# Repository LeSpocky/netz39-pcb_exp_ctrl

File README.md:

Laborssteuerung
===============

Steuergeräte für unser PCB-Labor

# AC Switch
µC-Steuerbares Relais für 230V-Geräte mit Feedback zum Stromfluss
Anschluss über I³C

# Power Board
alle passiven Schalter:
2x Relais für 230V-Anschluss (Deckenlicht, Luftpumpe Ätzbad)
4x FET für 12V (2x LED-Strip rot, 1x LED-Strip weiß, 1x UV-Licht)

PCB Exposure Control (alex)
====================
We have a box with 40 UV LEDs …

Parts
-----
* LP2950

ToDo
----
* add 74xx165 for input keys and optionally 74xx14 against contact bounce

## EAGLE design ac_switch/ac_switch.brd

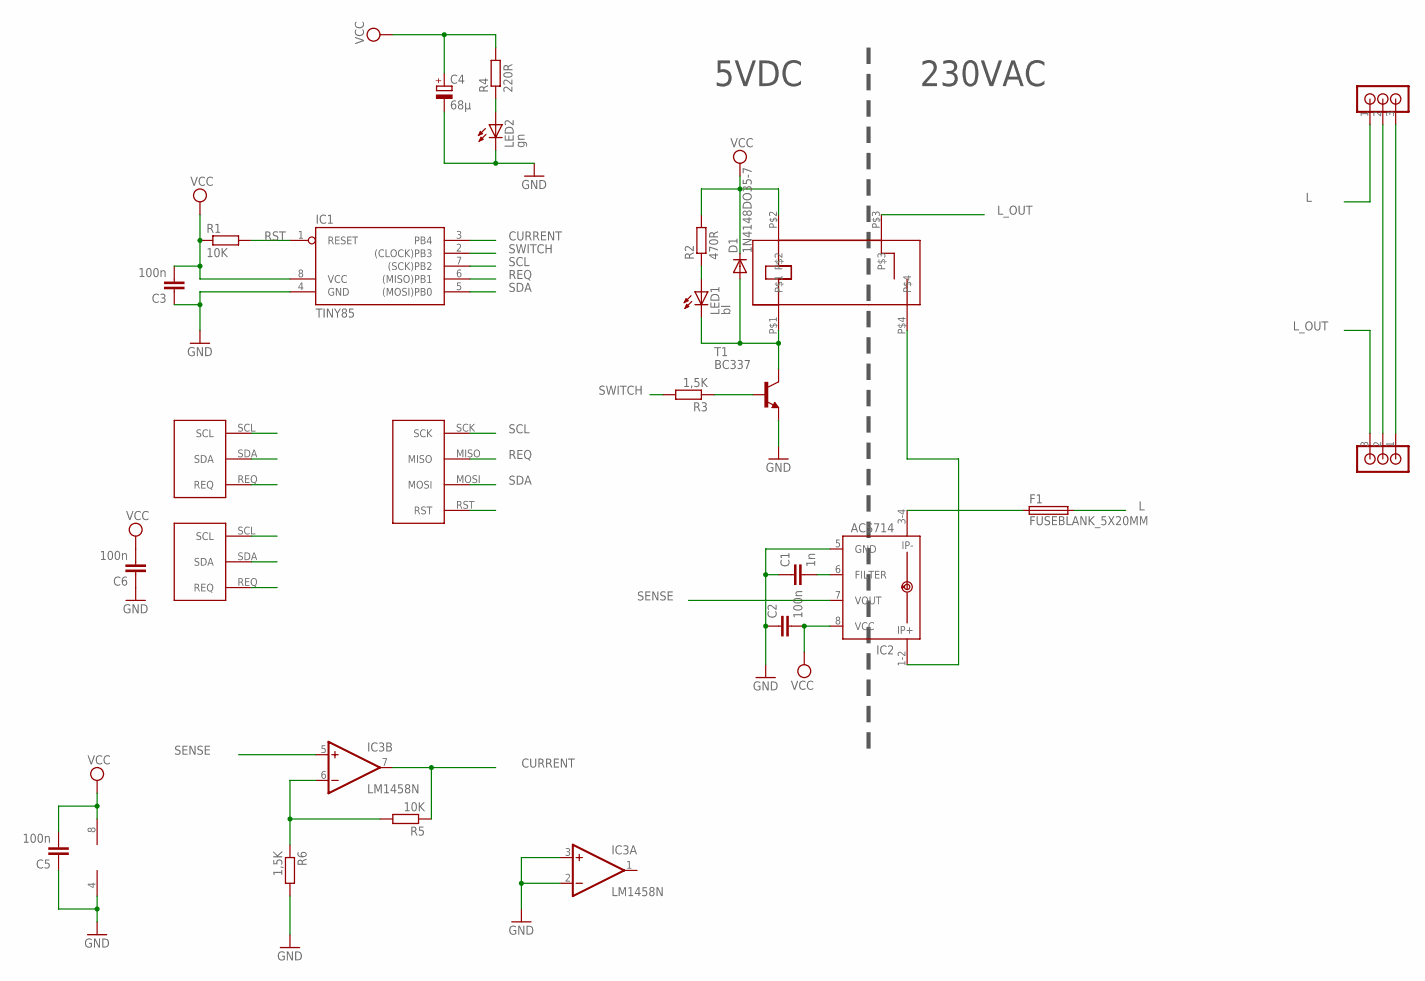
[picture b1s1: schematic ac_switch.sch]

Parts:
C1: 1n; C025-024X044
C2, C3, C5, C6: 100n; C025-024X044
C4: 68µ; E3,5-8
D1: 1N4148DO35-7; DO35-7
F1: FUSEBLANK_5X20MM; FUSE_HOLDER_5X20MM
IC1: TINY85; DIL08
IC2: ACS714
IC3: LM1458N; DIL08
LED1: bl; LED3MM
LED2: gn; LED3MM
R1: 10K; 0207/12
R2: 470R; 0207/10
R3, R6: 1,5K; 0207/10
R4: 220R; 0207/10
R5: 10K; 0207/10
T1: BC337; TO92
U$1: JS_05_MN_KT
U$2, U$6: RIACON_101_3
U$3, U$5: I3C_PORT; I3C_PADS
U$4: AVR_ISP

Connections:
CURRENT: IC1.3 (PB4), IC3.7 (OUT), R5.1
GND: C1.1, C2.1, C3.1, C4.-, C5.1, C6.1, IC1.4 (GND), IC2.5 (GND), IC3.2 (-IN), IC3.3 (+IN), IC3.4 (V-), LED2.K (C), R6.2, T1.1 (E), U$3.GND, U$4.GND, U$5.GND
L: F1.2, U$2.1
L_OUT: U$1.P$3, U$6.3
unnamed: D1.A, LED1.K (C), T1.3 (C), U$1.P$1
unnamed: C1.2, IC2.6 (FILTER)
unnamed: IC2.1-2 (IP+), U$1.P$4
unnamed: LED1.A, R2.1
unnamed: R3.1, T1.2 (B)
unnamed: LED2.A, R4.1
unnamed: F1.1, IC2.3-4 (IP-)
unnamed: U$2.3, U$6.1
unnamed: U$2.2, U$6.2
unnamed: IC3.6 (-IN), R5.2, R6.1
REQ: IC1.6 ((MISO)PB1), U$3.REQ, U$4.MISO, U$5.REQ
RST: IC1.1 (RESET), R1.2, U$4.RST
SCL: IC1.7 ((SCK)PB2), U$3.SCL, U$4.SCK, U$5.SCL
SDA: IC1.5 ((MOSI)PB0), U$3.SDA, U$4.MOSI, U$5.SDA
SENSE: IC2.7 (VOUT), IC3.5 (+IN)
SWITCH: IC1.2 ((CLOCK)PB3), R3.2
VCC: C2.2, C3.2, C4.+, C5.2, C6.2, D1.C, IC1.8 (VCC), IC2.8 (VCC), IC3.8 (V+), R1.1, R2.2, R4.2, U$1.P$2, U$3.VCC, U$4.VCC, U$5.VCC

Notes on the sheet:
230VAC
5VDC

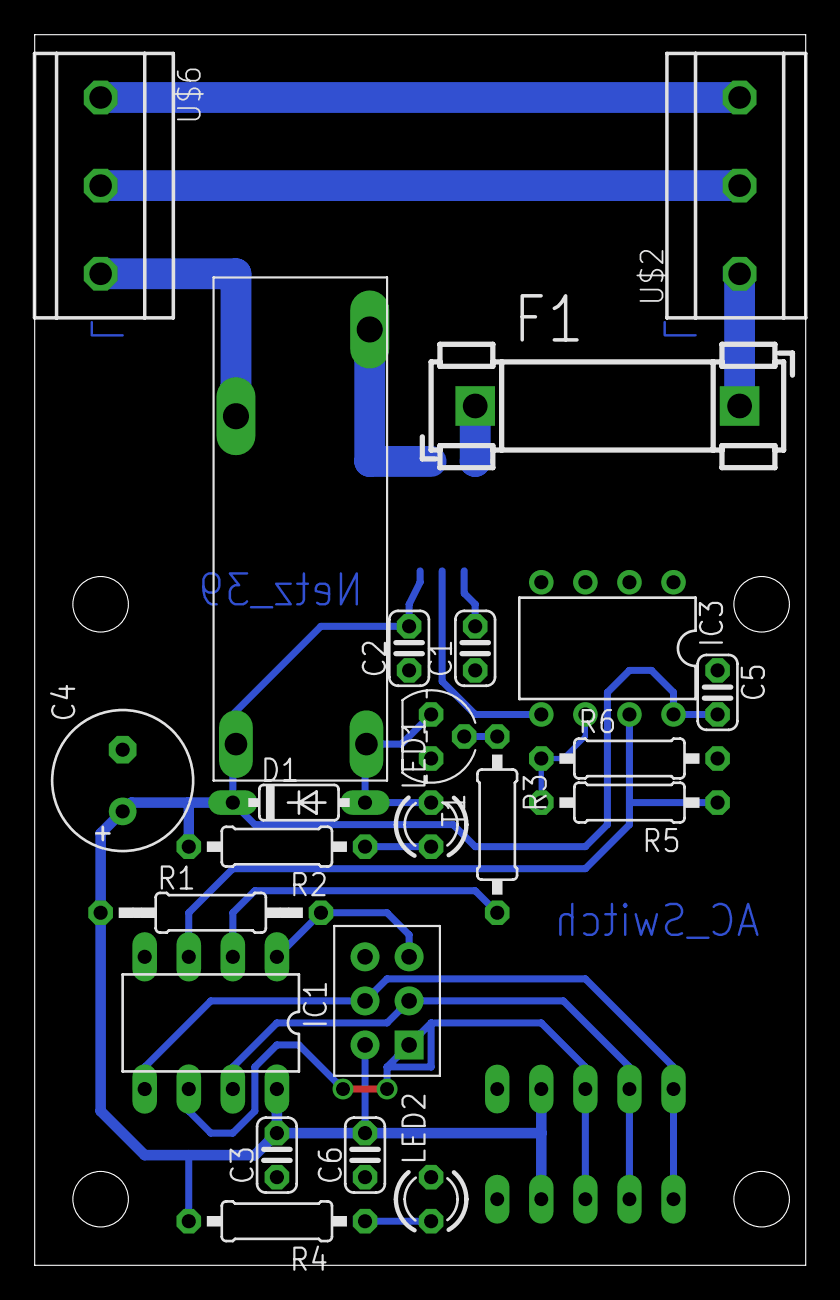
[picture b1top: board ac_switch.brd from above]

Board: 2 copper layers, 44.4 x 70.9 mm, 26 parts (1 on the bottom side), 21 nets.

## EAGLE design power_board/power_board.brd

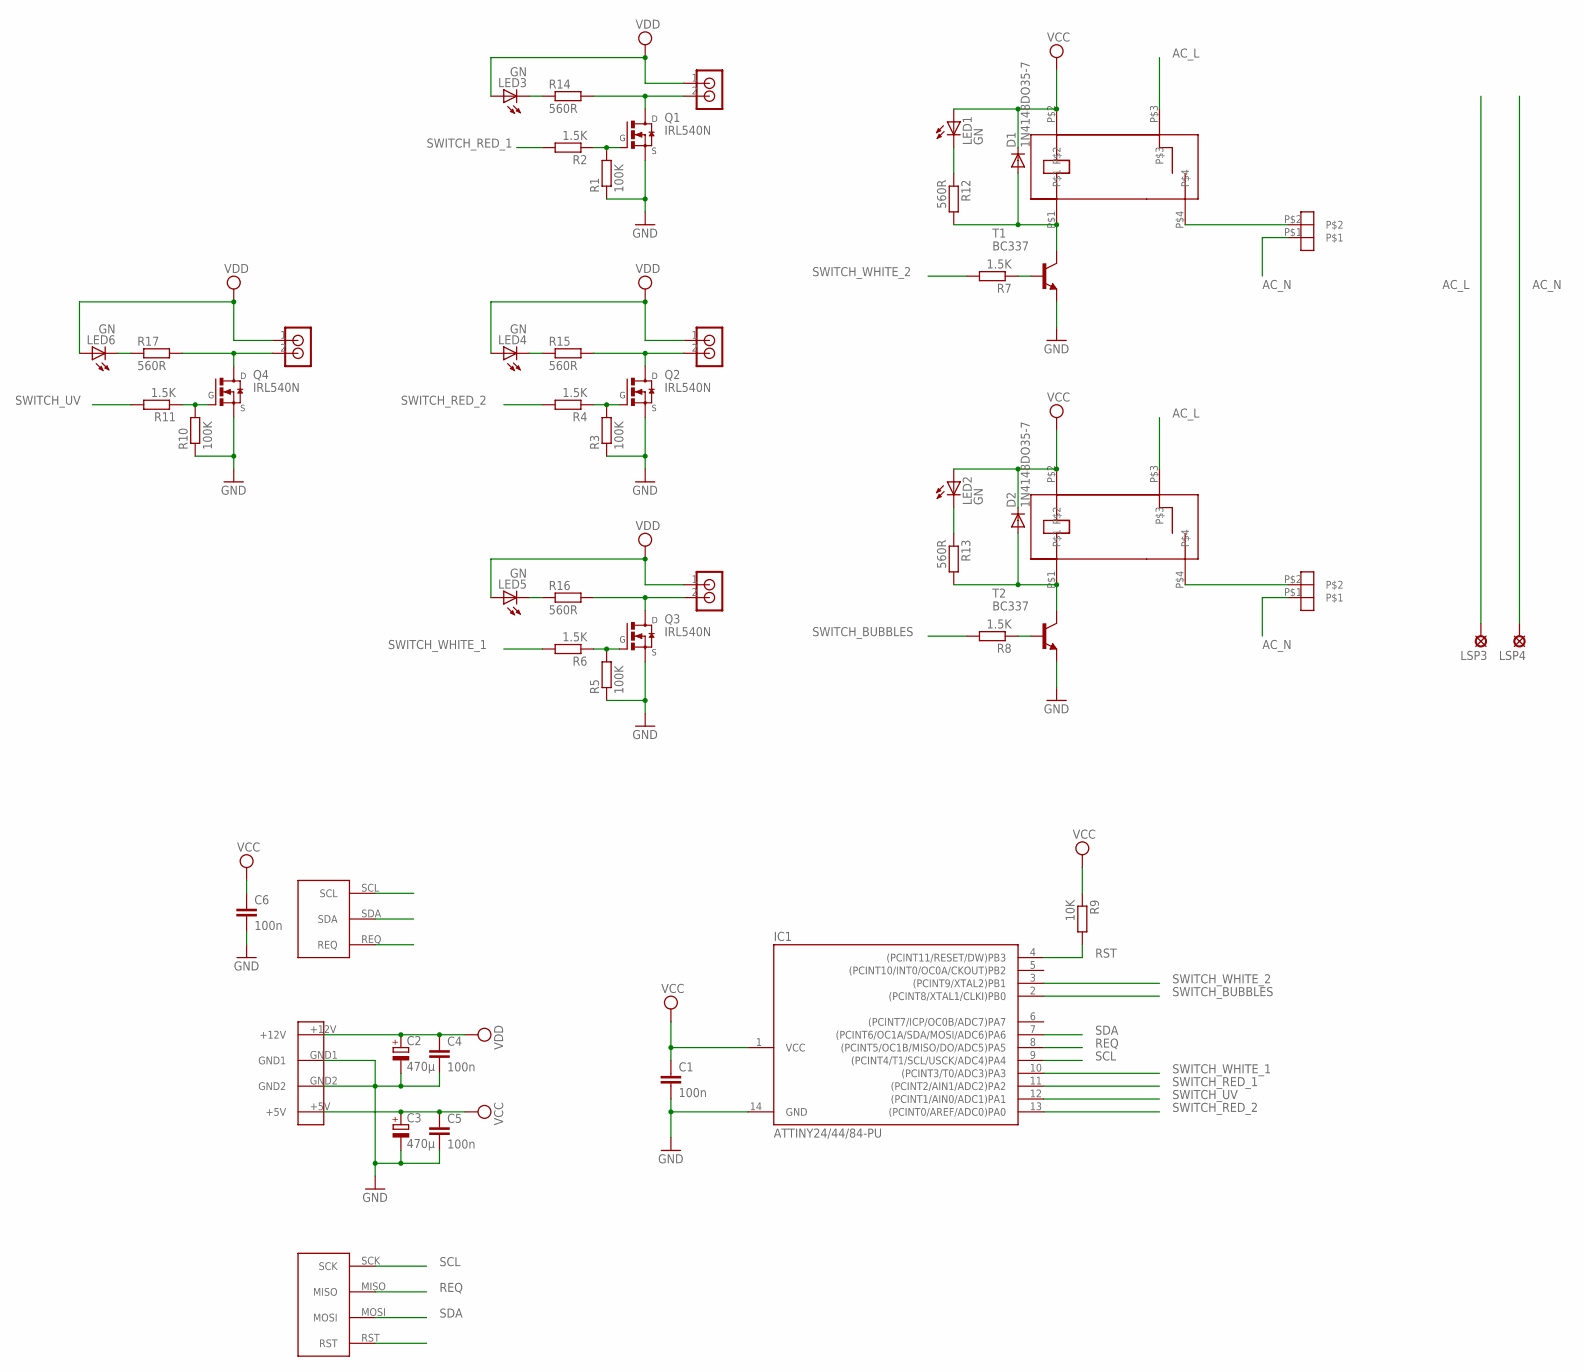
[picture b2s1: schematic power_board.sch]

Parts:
BUBBLES_RELAIS: WAGO_734_262
C1, C4, C5, C6: 100n; C025-024X044
C2, C3: 470µ; E3,5-10
D1, D2: 1N4148DO35-7; DO35-7
IC1: ATTINY24/44/84-PU; DIL14
LED1, LED2, LED3, LED4, LED5, LED6: GN; LED3MM
LSP3, LSP4: SE14
Q1, Q2, Q3, Q4: IRL540N; TO220V
R1, R3, R5, R10: 100K; 0204/5
R2, R4, R6, R11: 1.5K; 0204/5
R7, R8: 1.5K; 0204V
R9: 10K; 0207/10
R12, R13: 560R; 0204V
R14, R15, R16, R17: 560R; 0207/2V
RED_LED_1, RED_LED_2: RIACON_101_2
T1, T2: BC337; TO92
U$1: I3C_PORT; I3C_PADS
U$2, U$3: JS_05_MN_KT
U$4: PSW_5
U$5: AVR_ISP
UV_LED: RIACON_101_2
WHITE_LED: RIACON_101_2
WHITE_RELAIS: WAGO_734_262

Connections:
AC_L: LSP3.MP, U$2.P$3, U$3.P$3
AC_N: BUBBLES_RELAIS.P$1, LSP4.MP, WHITE_RELAIS.P$1
GND: C1.2, C2.-, C3.-, C4.2, C5.2, C6.2, IC1.14 (GND), Q1.3 (S), Q2.3 (S), Q3.3 (S), Q4.3 (S), R1.1, R3.1, R5.1, R10.1, T1.1 (E), T2.1 (E), U$1.GND, U$4.GND1, U$4.GND2, U$5.GND
unnamed: Q1.2 (D), R14.2, RED_LED_1.2
unnamed: Q2.1 (G), R3.2, R4.1
unnamed: Q1.1 (G), R1.2, R2.1
unnamed: Q2.2 (D), R15.2, RED_LED_2.2
unnamed: Q3.1 (G), R5.2, R6.1
unnamed: Q3.2 (D), R16.2, WHITE_LED.2
unnamed: R7.1, T1.2 (B)
unnamed: D1.A, R12.2, T1.3 (C), U$2.P$1
unnamed: R8.1, T2.2 (B)
unnamed: U$2.P$4, WHITE_RELAIS.P$2
unnamed: D2.A, R13.2, T2.3 (C), U$3.P$1
unnamed: BUBBLES_RELAIS.P$2, U$3.P$4
unnamed: Q4.1 (G), R10.2, R11.1
unnamed: Q4.2 (D), R17.2, UV_LED.2
unnamed: LED1.K (C), R12.1
unnamed: LED2.K (C), R13.1
unnamed: LED3.K (C), R14.1
unnamed: LED5.K (C), R16.1
unnamed: LED4.K (C), R15.1
unnamed: LED6.K (C), R17.1
REQ: IC1.8 ((PCINT5/OC1B/MISO/DO/ADC5)PA5), U$1.REQ, U$5.MISO
RST: IC1.4 ((PCINT11/RESET/DW)PB3), R9.2, U$5.RST
SCL: IC1.9 ((PCINT4/T1/SCL/USCK/ADC4)PA4), U$1.SCL, U$5.SCK
SDA: IC1.7 ((PCINT6/OC1A/SDA/MOSI/ADC6)PA6), U$1.SDA, U$5.MOSI
SWITCH_BUBBLES: IC1.2 ((PCINT8/XTAL1/CLKI)PB0), R8.2
SWITCH_RED_1: IC1.11 ((PCINT2/AIN1/ADC2)PA2), R2.2
SWITCH_RED_2: IC1.13 ((PCINT0/AREF/ADC0)PA0), R4.2
SWITCH_UV: IC1.12 ((PCINT1/AIN0/ADC1)PA1), R11.2
SWITCH_WHITE_1: IC1.10 ((PCINT3/T0/ADC3)PA3), R6.2
SWITCH_WHITE_2: IC1.3 ((PCINT9/XTAL2)PB1), R7.2
VCC: C1.1, C3.+, C5.1, C6.1, D1.C, D2.C, IC1.1 (VCC), LED1.A, LED2.A, R9.1, U$1.VCC, U$2.P$2, U$3.P$2, U$4.+5V, U$5.VCC
VDD: C2.+, C4.1, LED3.A, LED4.A, LED5.A, LED6.A, RED_LED_1.1, RED_LED_2.1, U$4.+12V, UV_LED.1, WHITE_LED.1

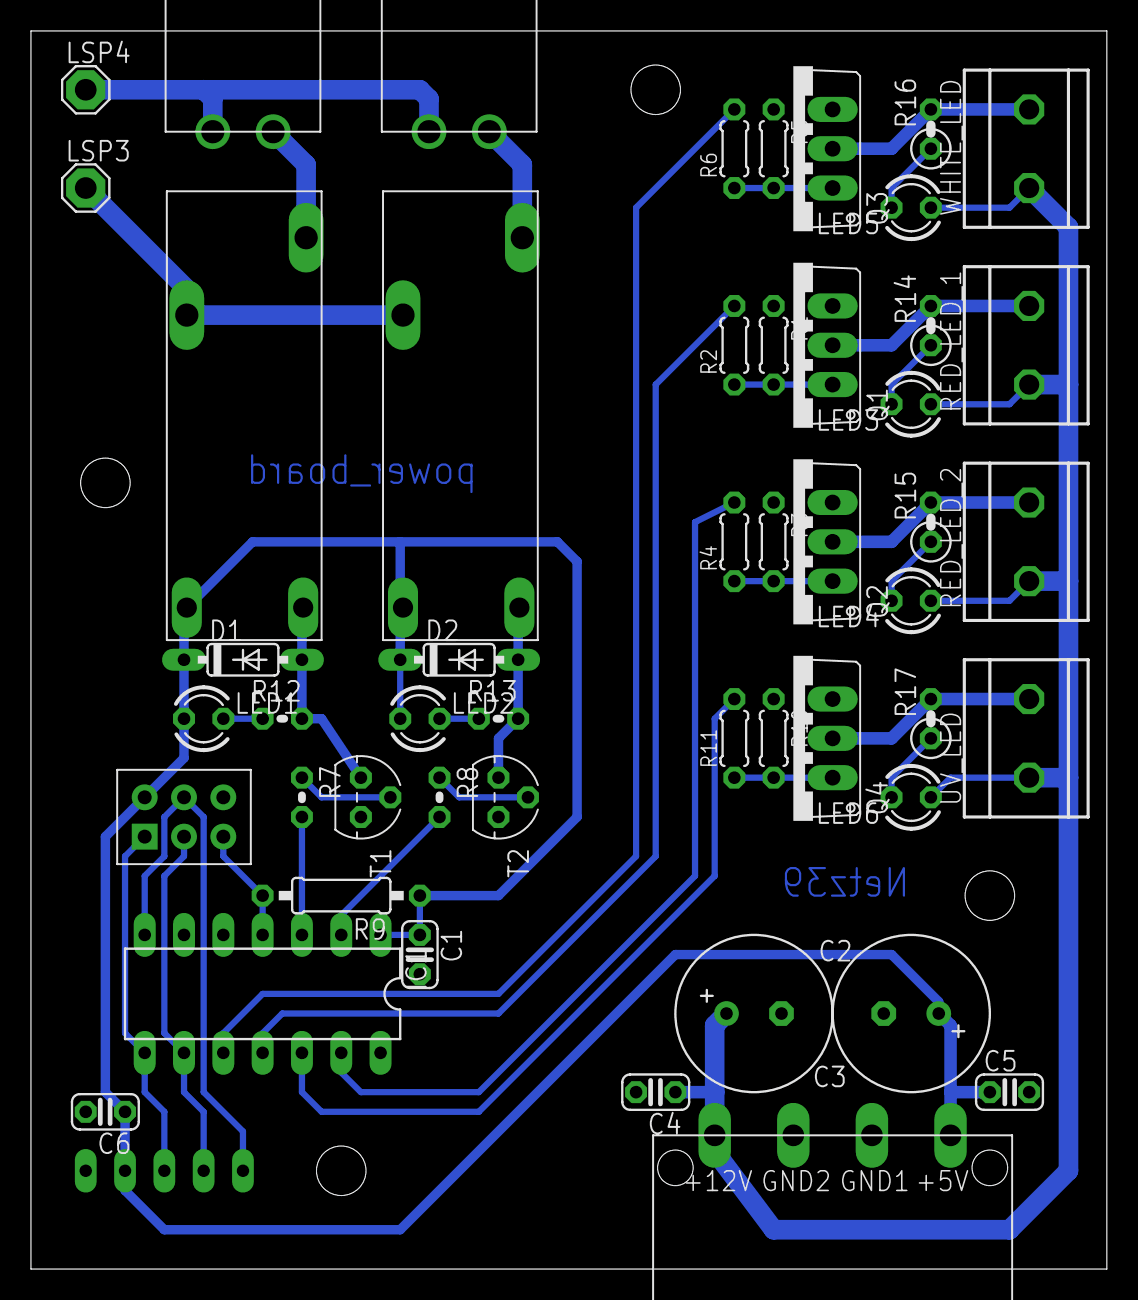
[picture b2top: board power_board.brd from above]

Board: 2 copper layers, 69.5 x 80.0 mm, 51 parts (0 on the bottom side), 35 nets.

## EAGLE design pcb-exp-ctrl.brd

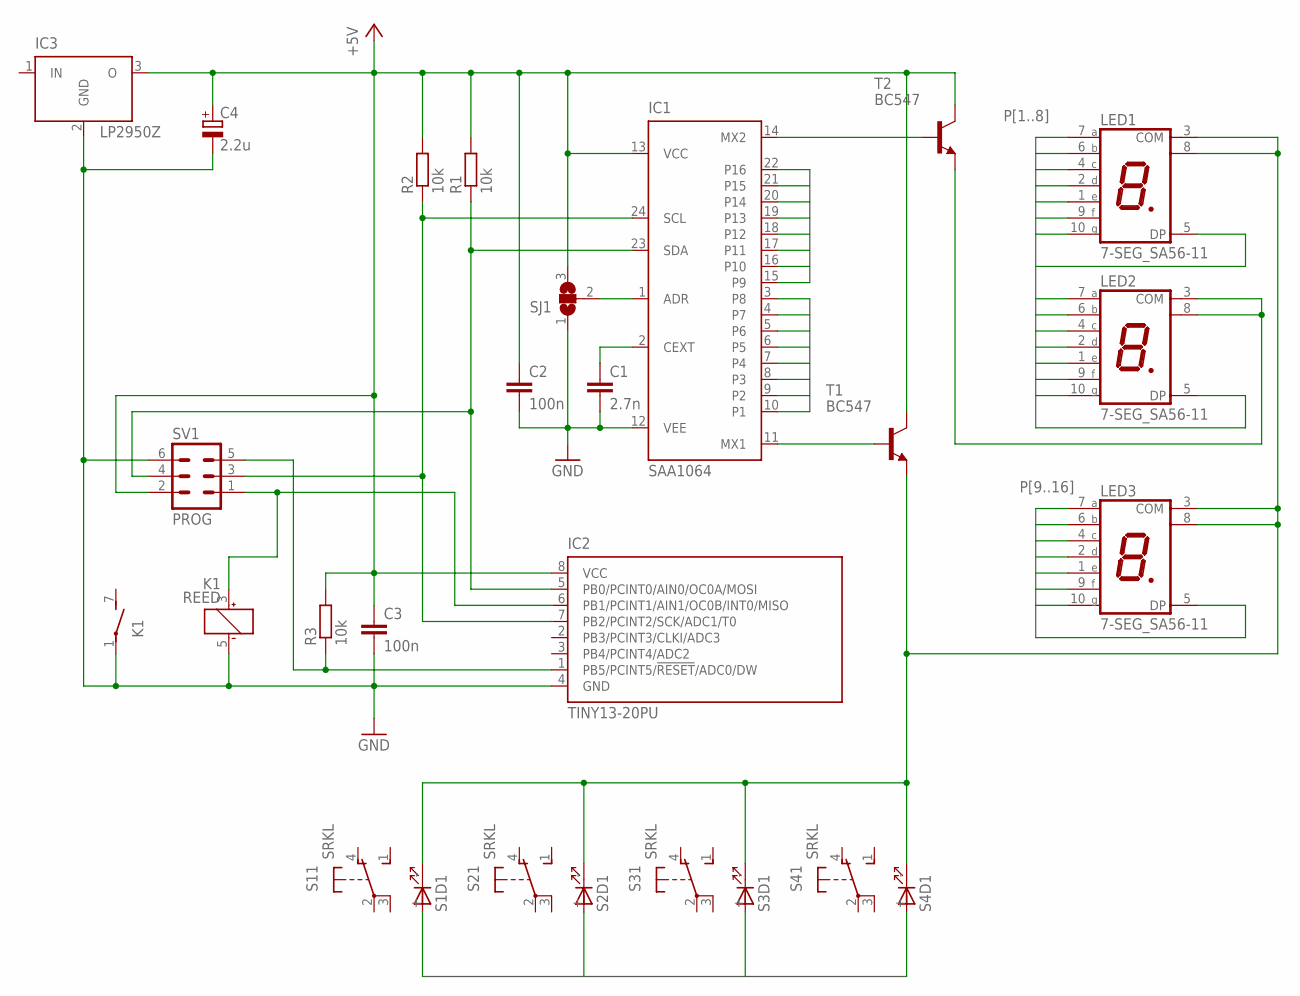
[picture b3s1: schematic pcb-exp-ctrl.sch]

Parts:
C1: 2.7n; C025-025X050
C2, C3: 100n; C025-025X050
C4: 2.2u; E2,5-6
IC1: SAA1064; DIL24-6
IC2: TINY13-20PU; DIL08
IC3: LP2950Z; TO92
K1: REED
LED1, LED2, LED3: 7-SEG_SA56-11; SA56-11
R1, R2, R3: 10k; 0204/7
S1, S2, S3, S4: SRKL
SJ1: SJ2W; SJ_2
SV1: PROG; ML6
T1, T2: BC547; TO92

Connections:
+5V: C2.1, C3.1, C4.+, IC1.13 (VCC), IC2.8 (VCC), IC3.3 (O), R1.2, R2.2, R3.2, SJ1.3, SV1.2, T1.3 (C), T2.3 (C)
GND: C1.2, C2.2, C3.2, C4.-, IC1.12 (VEE), IC2.4 (GND), IC3.2 (GND), K1.1, K1.5 (-), SJ1.1, SV1.6
MISO: IC2.6 (PB1/PCINT1/AIN1/OC0B/INT0/MISO), K1.3 (+), SV1.1
MOSI: IC1.23 (SDA), IC2.5 (PB0/PCINT0/AIN0/OC0A/MOSI), R1.1, SV1.4
unnamed: LED2.3 (COM), LED2.8 (COM), T2.1 (E)
unnamed: C1.1, IC1.2 (CEXT)
unnamed: IC1.1 (ADR), SJ1.2
unnamed: LED1.3 (COM), LED1.8 (COM), LED3.3 (COM), LED3.8 (COM), S1.- (C), S2.- (C), S3.- (C), S4.- (C), T1.1 (E)
unnamed: IC1.11 (MX1), T1.2 (B)
unnamed: IC1.14 (MX2), T2.2 (B)
P1: IC1.10 (P1), LED1.7 (A), LED2.7 (A)
P2: IC1.9 (P2), LED1.6 (B), LED2.6 (B)
P3: IC1.8 (P3), LED1.4 (C), LED2.4 (C)
P4: IC1.7 (P4), LED1.2 (D), LED2.2 (D)
P5: IC1.6 (P5), LED1.1 (E), LED2.1 (E)
P6: IC1.5 (P6), LED1.9 (F), LED2.9 (F)
P7: IC1.4 (P7), LED1.10 (G), LED2.10 (G)
P8: IC1.3 (P8), LED1.5 (DP), LED2.5 (DP)
P9: IC1.15 (P9), LED3.7 (A), S1.+ (A)
P10: IC1.16 (P10), LED3.6 (B), S2.+ (A)
P11: IC1.17 (P11), LED3.4 (C), S3.+ (A)
P12: IC1.18 (P12), LED3.2 (D), S4.+ (A)
P13: IC1.19 (P13), LED3.1 (E)
P14: IC1.20 (P14), LED3.9 (F)
P15: IC1.21 (P15), LED3.10 (G)
P16: IC1.22 (P16), LED3.5 (DP)
SCK: IC1.24 (SCL), IC2.7 (PB2/PCINT2/SCK/ADC1/T0), R2.1, SV1.3
_RESET: IC2.1 (PB5/PCINT5/!RESET!/ADC0/DW), R3.1, SV1.5

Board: 2 copper layers, 22 parts (1 on the bottom side), 28 nets, no tracks yet.

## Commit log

2013-03-11 initial with just uC, 7seg and LED driver
2013-03-12 connect saa1064
2013-03-12 add 100n capacities for ICs
2013-03-12 add programmer header and connect to uC
2013-03-14 added parts from bread board to list
2013-03-15 drei Taster nebst integrierten LEDs hinzugefügt und teilverdrahtet
2013-03-15 spannungsregler nebst elko hinzugefügt
2013-03-15 add NPN for switching UV LEDs
2013-03-18 replace NPN with relay
2013-03-19 extra LEDs korrekt verdrahtet
2013-08-01 move pcb and src files to separate folders
2013-08-01 prepare source for further hacking
2013-08-02 test on breadboard with different uC
2013-12-29 PCB-Expositionssteuerung von Alex in ein Unterverzeichnis geschoben
2013-12-29 Konzept Bedienkomponenten
2013-12-29 Hinweis zum Verzeichnis ac_switch
2013-12-30 Erster Entwurf AC-Switch
2013-12-30 schaltung AC-Switch 98% fertig
2013-12-30 Beschreibung AC-Switch angepasst
2013-12-30 weiterer I³C-Port
2013-12-30 PCB-Routing
2013-12-31 * Transistor in Emitterschaltung (dann mit Vorwiderstand)
2013-12-31 * Werte für Widerstände und Kondensator (inkl. Package) angepasst * fine-tuning am PCB-Layout
2013-12-31 Overlap behoben
2013-12-31 Jetzt auch mit den richtigen Anschlussklemmen
2014-01-04 Power-Board: alle Schalter, die keine Verbrauchsmessung haben (230V und 12V)
2014-01-04 Beschreibung in readme eingefügt
2014-01-04 Board-Abmessungen auf gerade Werte gesetzt Beschriftung Befestigung etwas verschoben
2014-01-04 Platinenlayout angepasst, sodass es zum Power-Board passt
2014-01-05 Positionen der Lötpunkte für AC angepasst, sodass die Boards zueinander passen mehr Platz um die Lötbrücke
2014-04-16 Power-Board: * Widerstands-Packages korrigiert * Power-LED eingefügt
2014-05-04 AC switch: re-routing
2014-05-08 Added a fuse and an OP amp to increase signal bandwith.
